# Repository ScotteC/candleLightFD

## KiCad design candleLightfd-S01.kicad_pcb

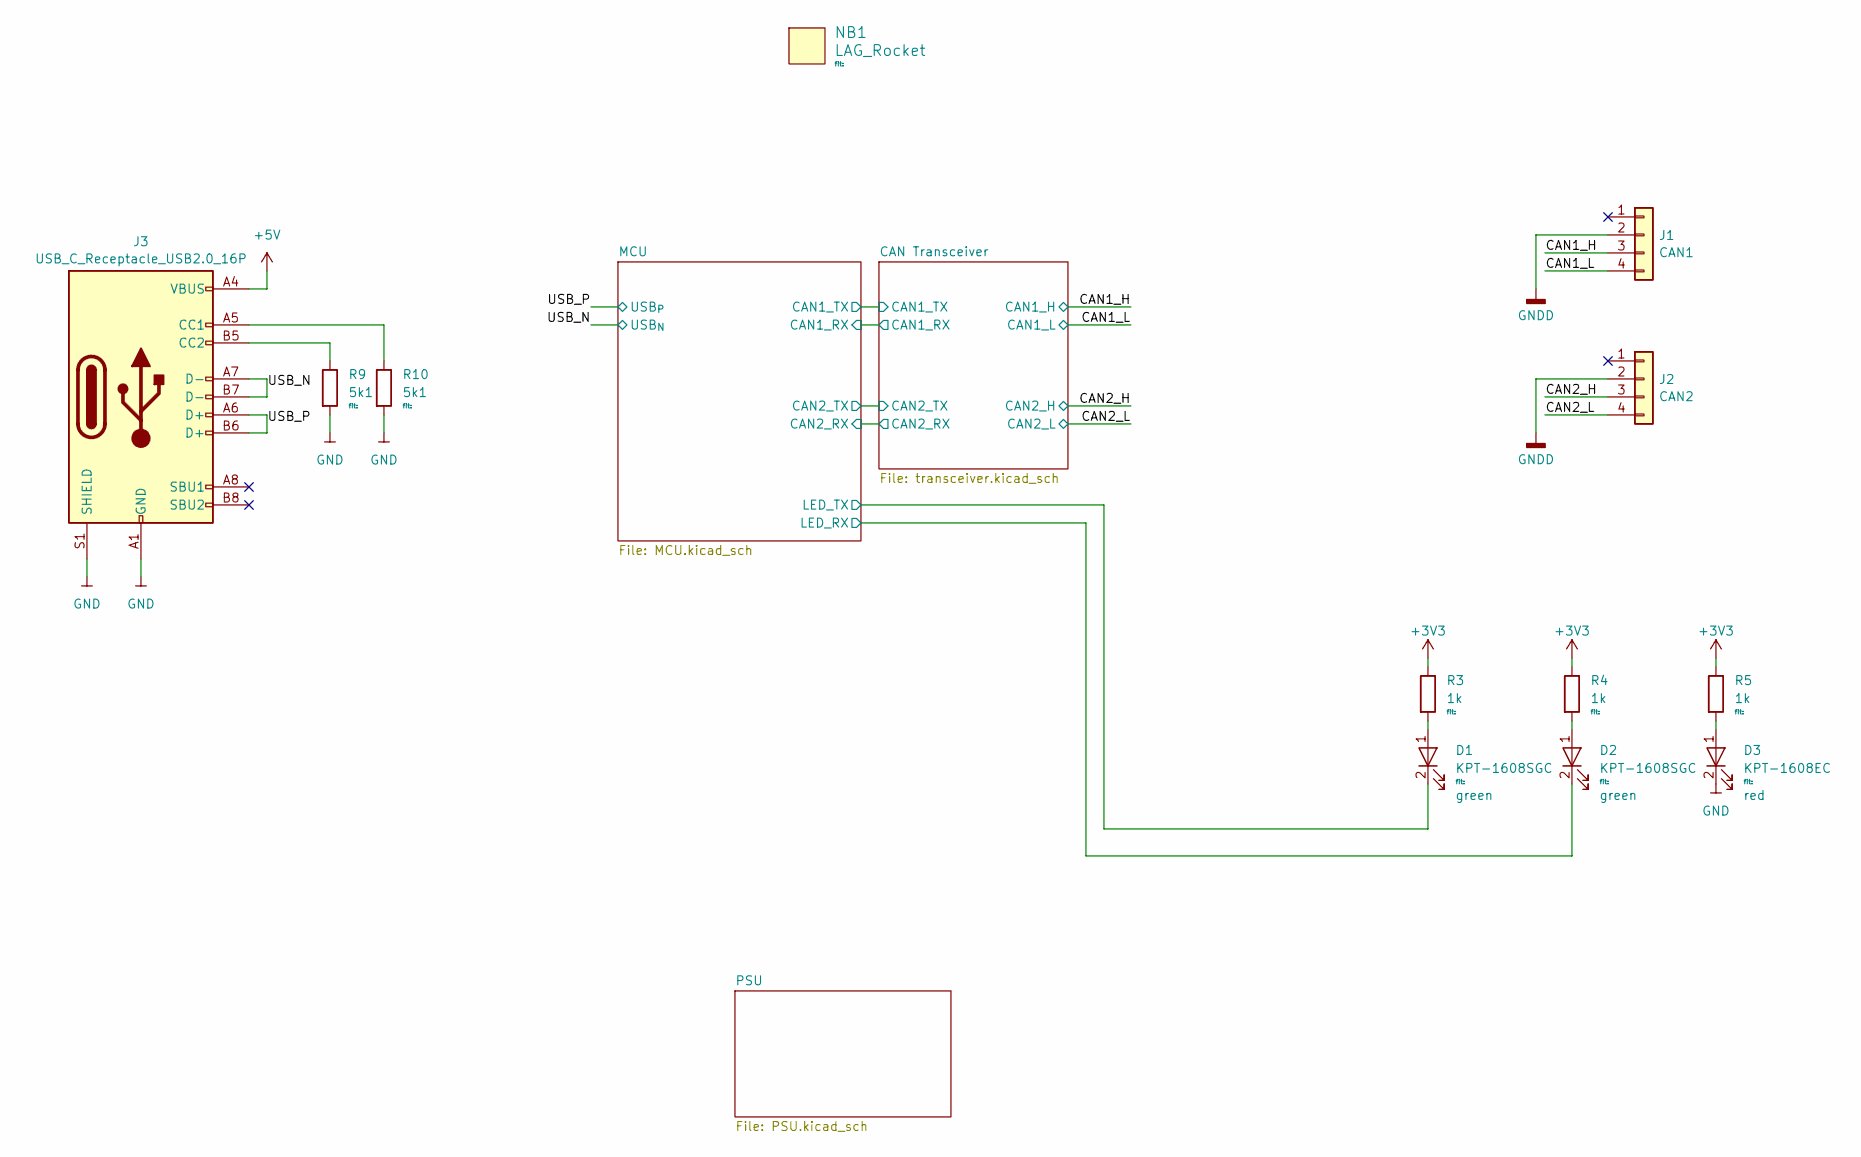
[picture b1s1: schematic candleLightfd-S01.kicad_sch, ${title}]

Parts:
D1, D2: KPT-1608SGC; LED_0603_1608Metric; MPN KPT-1608SGC
D3: KPT-1608EC; LED_0603_1608Metric; MPN KPT-1608EC
J1: CAN1; PSS254_1x04_Horizontal
J2: CAN2; PSS254_1x04_Horizontal
J3: USB_C_Receptacle_USB2.0_16P; USB_C_Receptacle_GCT_USB4085; MPN GSB1C411111DS1HR; mouser 523-GSB1C411111DS1HR
NB1: LAG_Rocket; lag_rocket_14.5mmx15mm
R3, R4, R5: 1k; R_0603_1608Metric
R9, R10: 5k1; R_0603_1608Metric

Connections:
+3V3: R3.1, R4.1, R5.1; also elsewhere on the board
+5V: J3.A4 (VBUS), J3.A9 (VBUS), J3.B4 (VBUS), J3.B9 (VBUS); also elsewhere on the board
/CAN1_H: J1.3; also elsewhere on the board
/CAN1_L: J1.4; also elsewhere on the board
/CAN2_H: J2.3; also elsewhere on the board
/CAN2_L: J2.4; also elsewhere on the board
/MCU/LED_RX: D2.2 (K); also elsewhere on the board
/MCU/LED_TX: D1.2 (K); also elsewhere on the board
/USB_N: J3.A7 (D-), J3.B7 (D-); also elsewhere on the board
/USB_P: J3.A6 (D+), J3.B6 (D+); also elsewhere on the board
GND: D3.2 (K), J3.A1 (GND), J3.A12 (GND), J3.B1 (GND), J3.B12 (GND), J3.S1 (SHIELD), R9.2, R10.2; also elsewhere on the board
GNDD: J1.2, J2.2; also elsewhere on the board
unnamed: D1.1 (A), R3.2
unnamed: D2.1 (A), R4.2
unnamed: D3.1 (A), R5.2
unnamed: J3.A5 (CC1), R10.1
unnamed: J3.B5 (CC2), R9.1

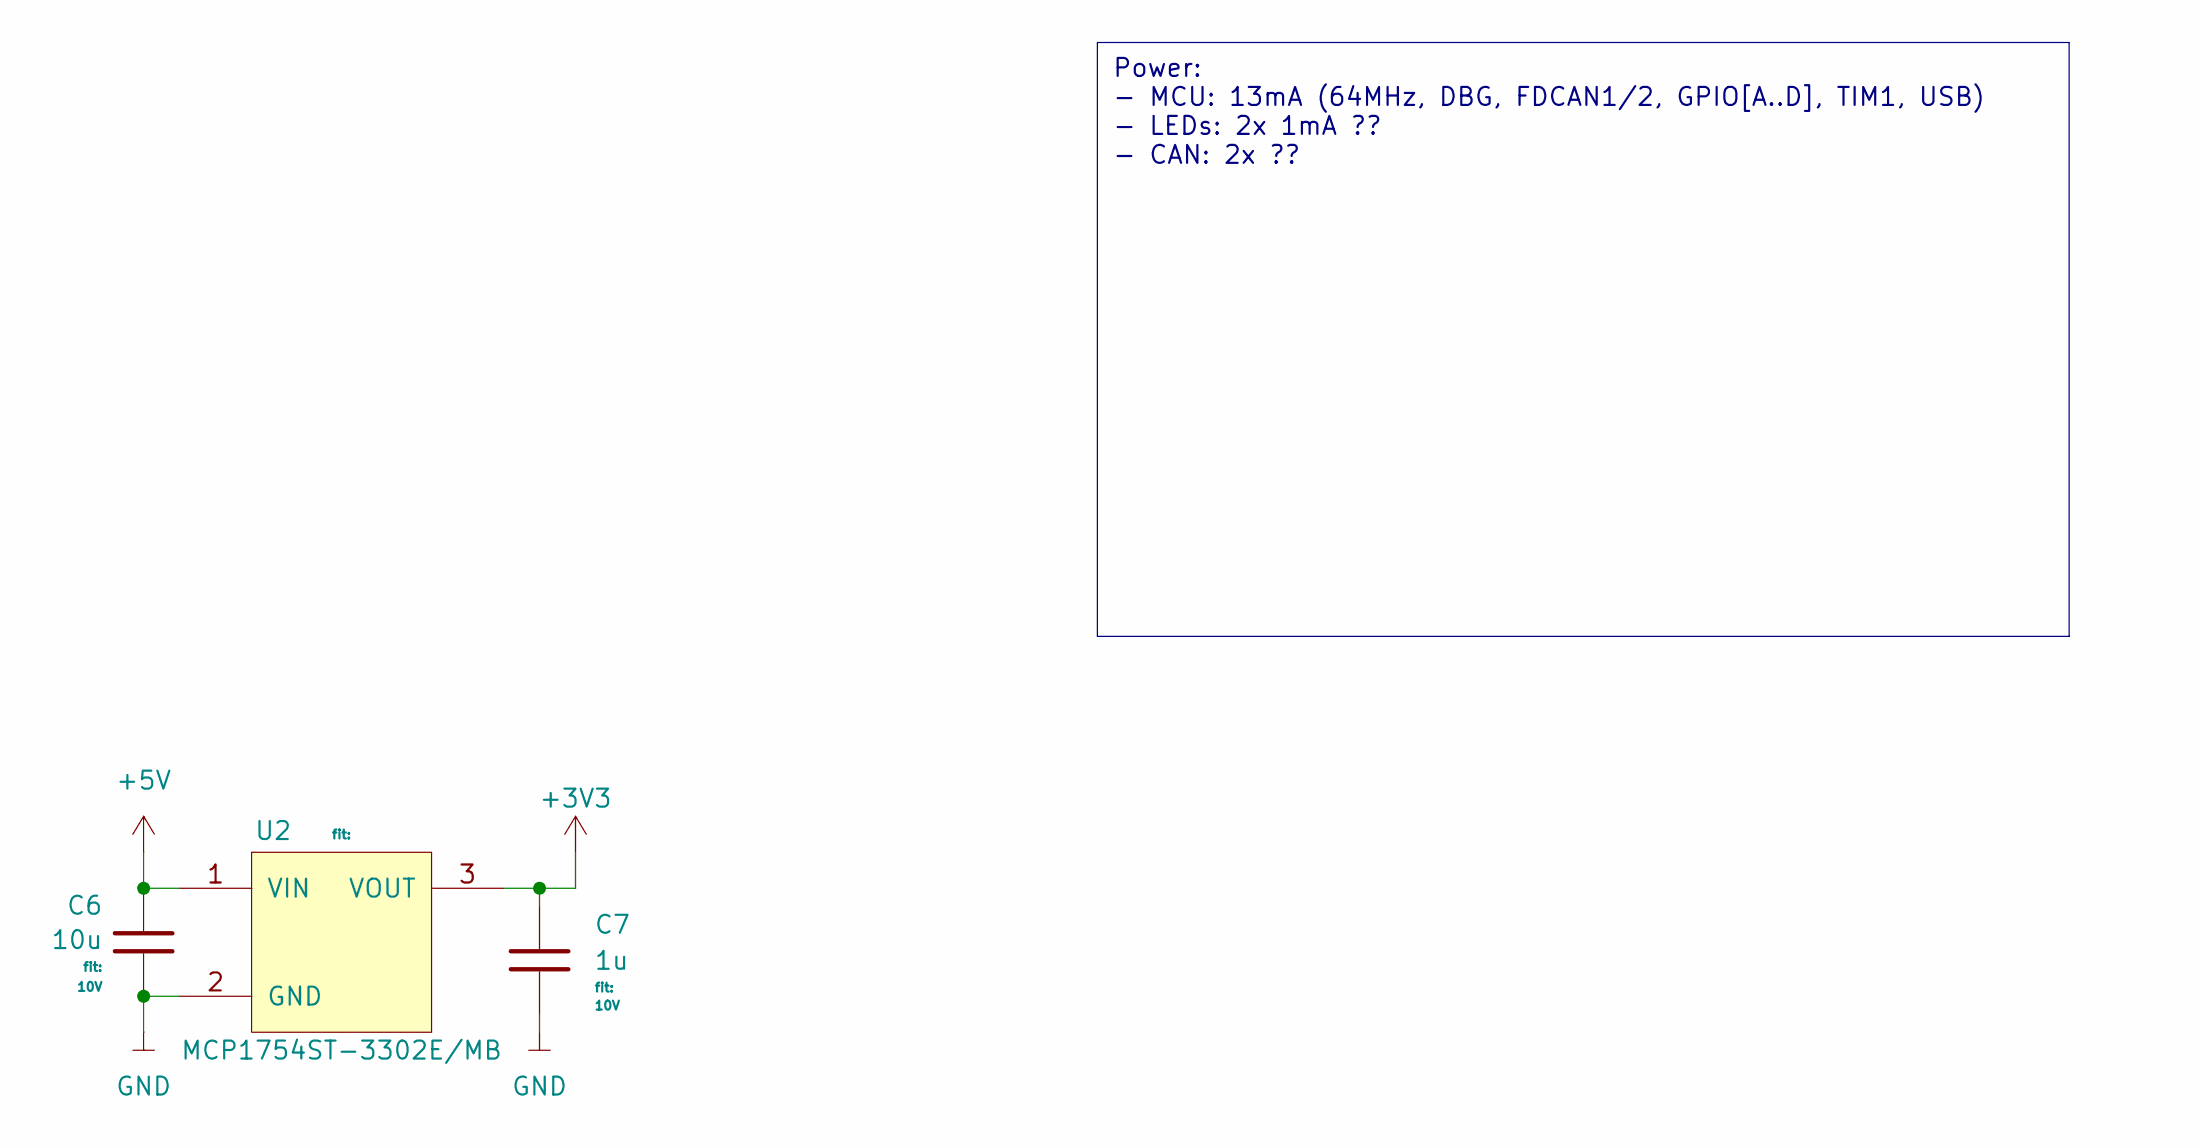
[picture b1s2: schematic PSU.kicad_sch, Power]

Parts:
C6: 10u; C_0603_1608Metric; MPN any
C7: 1u; C_0603_1608Metric; MPN any
U2: MCP1754ST-3302E/MB; SOT-89-3; MPN MCP1754ST-3302E/MB; digikey MCP1754ST-3302E/MBCT-ND

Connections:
+3V3: C7.1, U2.3 (VOUT); also elsewhere on the board
+5V: C6.1, U2.1 (VIN); also elsewhere on the board
GND: C6.2, C7.2, U2.2 (GND); also elsewhere on the board

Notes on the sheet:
Power: - MCU: 13mA (64MHz, DBG, FDCAN1/2, GPIO[A..D], TIM1, USB) - LEDs: 2x 1mA ?? - CAN: 2x ??

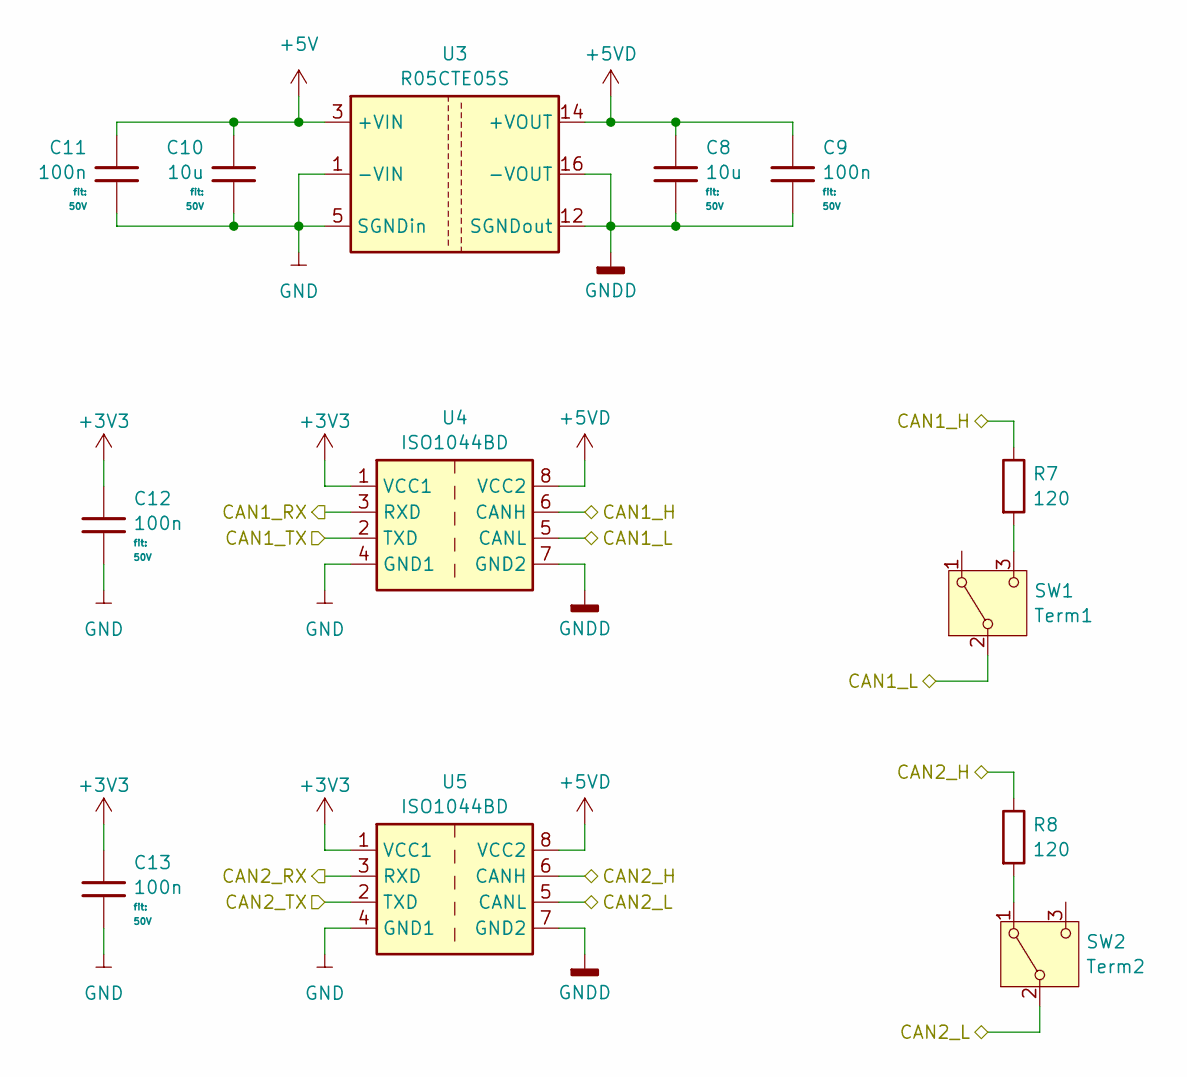
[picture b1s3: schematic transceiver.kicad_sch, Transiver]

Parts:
C8, C10: 10u; C_0603_1608Metric; MPN any
C9, C11, C12, C13: 100n; C_0603_1608Metric; MPN any
R7, R8: 120; R_0603_1608Metric
SW1: Term1; SW_Slide_SPDT_Angled_CK_OS102011MA1Q; MPN OS102011MA1QS1; digikey CKN9560-ND
SW2: Term2; SW_Slide_SPDT_Angled_CK_OS102011MA1Q; MPN OS102011MA1QS1; digikey CKN9560-ND
U3: R05CTE05S; SOIC-16W_7.5x10.3mm_P1.27mm; MPN R05CTE05S-R; digikey 945-R05CTE05S-RCT-ND
U4, U5: ISO1044BD; SOIC-8_3.9x4.9mm_P1.27mm; MPN ISO1044BDR; digikey 296-ISO1044BDRCT-ND

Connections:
+3V3: C12.1, C13.1, U4.1 (VCC1), U5.1 (VCC1); also elsewhere on the board
+5V: C10.1, C11.1, U3.3 (+VIN), U3.4 (+VIN); also elsewhere on the board
+5VD: C8.1, C9.1, U3.13 (+VOUT), U3.14 (+VOUT), U4.8 (VCC2), U5.8 (VCC2)
/CAN1_H: R7.1, U4.6 (CANH); also elsewhere on the board
/CAN1_L: SW1.2 (B), U4.5 (CANL); also elsewhere on the board
/CAN2_H: R8.1, U5.6 (CANH); also elsewhere on the board
/CAN2_L: SW2.2 (B), U5.5 (CANL); also elsewhere on the board
/CAN Transceiver/CAN1_RX: U4.3 (RXD); also elsewhere on the board
/CAN Transceiver/CAN1_TX: U4.2 (TXD); also elsewhere on the board
/CAN Transceiver/CAN2_RX: U5.3 (RXD); also elsewhere on the board
/CAN Transceiver/CAN2_TX: U5.2 (TXD); also elsewhere on the board
GND: C10.2, C11.2, C12.2, C13.2, U3.1 (-VIN), U3.2 (-VIN), U3.5 (SGNDin), U3.6 (SGNDin), U3.7 (SGNDin), U3.8 (SGNDin), U4.4 (GND1), U5.4 (GND1); also elsewhere on the board
GNDD: C8.2, C9.2, U3.9 (SGNDout), U3.11 (SGNDout), U3.12 (SGNDout), U3.15 (-VOUT), U3.16 (-VOUT), U4.7 (GND2), U5.7 (GND2); also elsewhere on the board
unnamed: R7.2, SW1.3 (C)
unnamed: R8.2, SW2.1 (A)

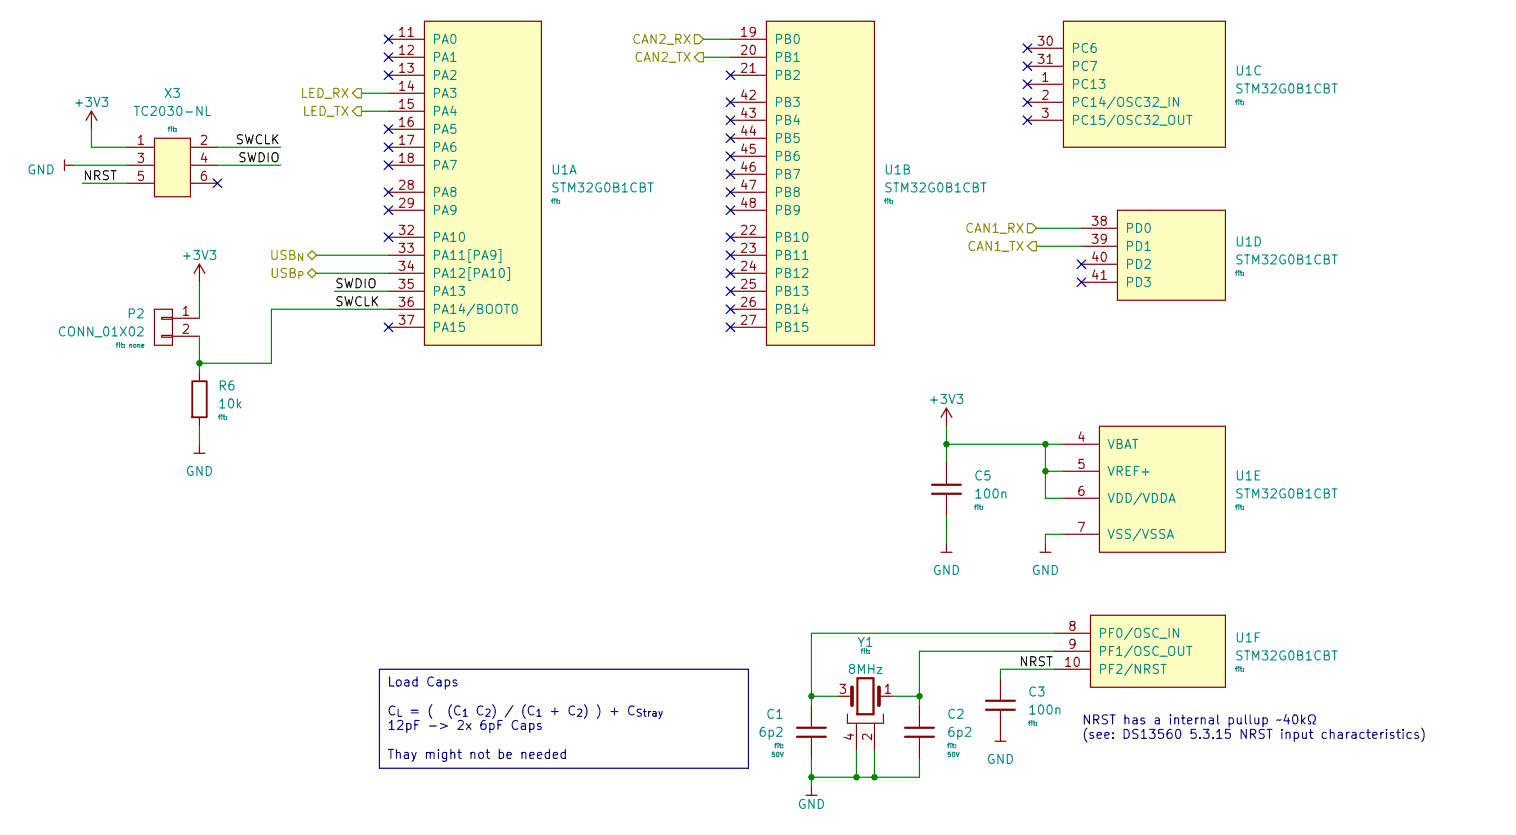
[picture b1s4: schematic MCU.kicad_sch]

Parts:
C1, C2: 6p2; C_0603_1608Metric; MPN CC0603BRNPO9BN6R2; digikey 13-CC0603BRNPO9BN6R2CT-ND
C3, C5: 100n; C_0603_1608Metric; MPN any
P2: CONN_01X02; SolderJumper-2_P1.3mm_Open_RoundedPad1.0x1.5mm; MPN generic
R6: 10k; R_0603_1608Metric
U1: STM32G0B1CBT; LQFP-48_7x7mm_P0.5mm; MPN STM32G0B1CBT; mouser 511-STM32G0B1CBT3
X3: TC2030-NL; MPN TC2030-NL
Y1: 830108313809; Crystal_SMD_3225-4Pin_3.2x2.5mm; MPN 830108313809; mouser 710-830108313809

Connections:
+3V3: C5.1, P2.1, U1.4 (VBAT), U1.5 (VREF+), U1.6 (VDD/VDDA), X3.1; also elsewhere on the board
/CAN Transceiver/CAN1_RX: U1.38 (PD0); also elsewhere on the board
/CAN Transceiver/CAN1_TX: U1.39 (PD1); also elsewhere on the board
/CAN Transceiver/CAN2_RX: U1.19 (PB0); also elsewhere on the board
/CAN Transceiver/CAN2_TX: U1.20 (PB1); also elsewhere on the board
/MCU/LED_RX: U1.14 (PA3); also elsewhere on the board
/MCU/LED_TX: U1.15 (PA4); also elsewhere on the board
/MCU/NRST: C3.1, U1.10 (PF2/NRST), X3.5 (P4)
/MCU/SWCLK: P2.2, R6.1, U1.36 (PA14/BOOT0), X3.2
/MCU/SWDIO: U1.35 (PA13), X3.4
/USB_N: U1.33 (PA11[PA9]); also elsewhere on the board
/USB_P: U1.34 (PA12[PA10]); also elsewhere on the board
GND: C1.1, C2.1, C3.2, C5.2, R6.2, U1.7 (VSS/VSSA), X3.3, Y1.2 (GND), Y1.4 (GND); also elsewhere on the board
unnamed: C1.2, U1.8 (PF0/OSC_IN), Y1.3 (C_{2})
unnamed: C2.2, U1.9 (PF1/OSC_OUT), Y1.1 (C_{1})

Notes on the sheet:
Load Caps C_{L} = ( (C_{1} C_{2}) / (C_{1} + C_{2}) ) + C_{Stray} 12pF -> 2x 6pF Caps Thay might not be needed
NRST has a internal pullup ~40kΩ (see: DS13560 5.3.15 NRST input characteristics)

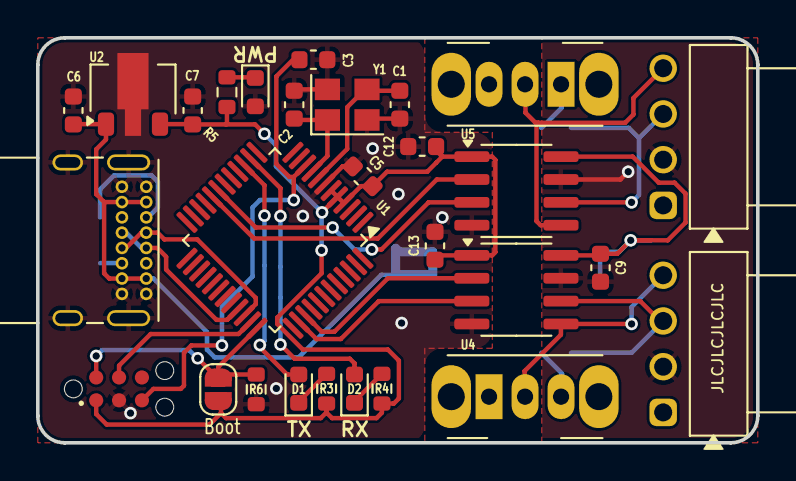
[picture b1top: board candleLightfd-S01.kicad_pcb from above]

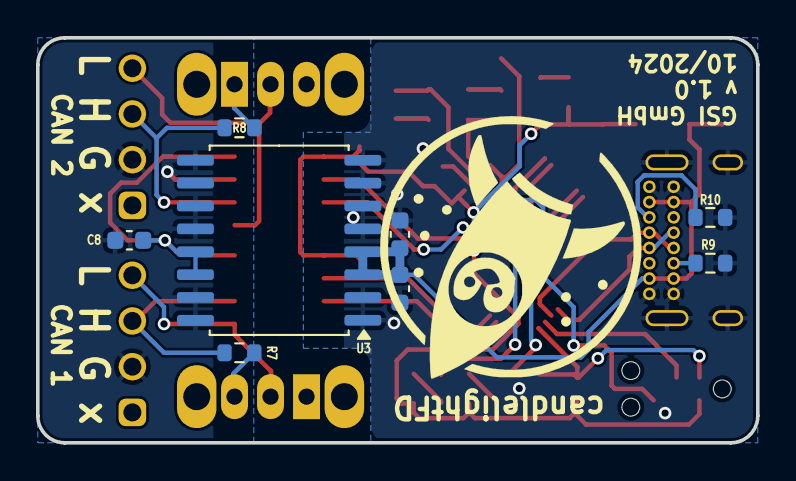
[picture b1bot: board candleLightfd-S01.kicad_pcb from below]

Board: 2 copper layers, 40.0 x 22.5 mm, 37 parts (9 on the bottom side), 29 nets.

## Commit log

2024-10-15 clean up
2024-10-15 gsi-v1
2024-10-15 replace connector CAN1/2 with PSS
2024-10-16 ready for production
